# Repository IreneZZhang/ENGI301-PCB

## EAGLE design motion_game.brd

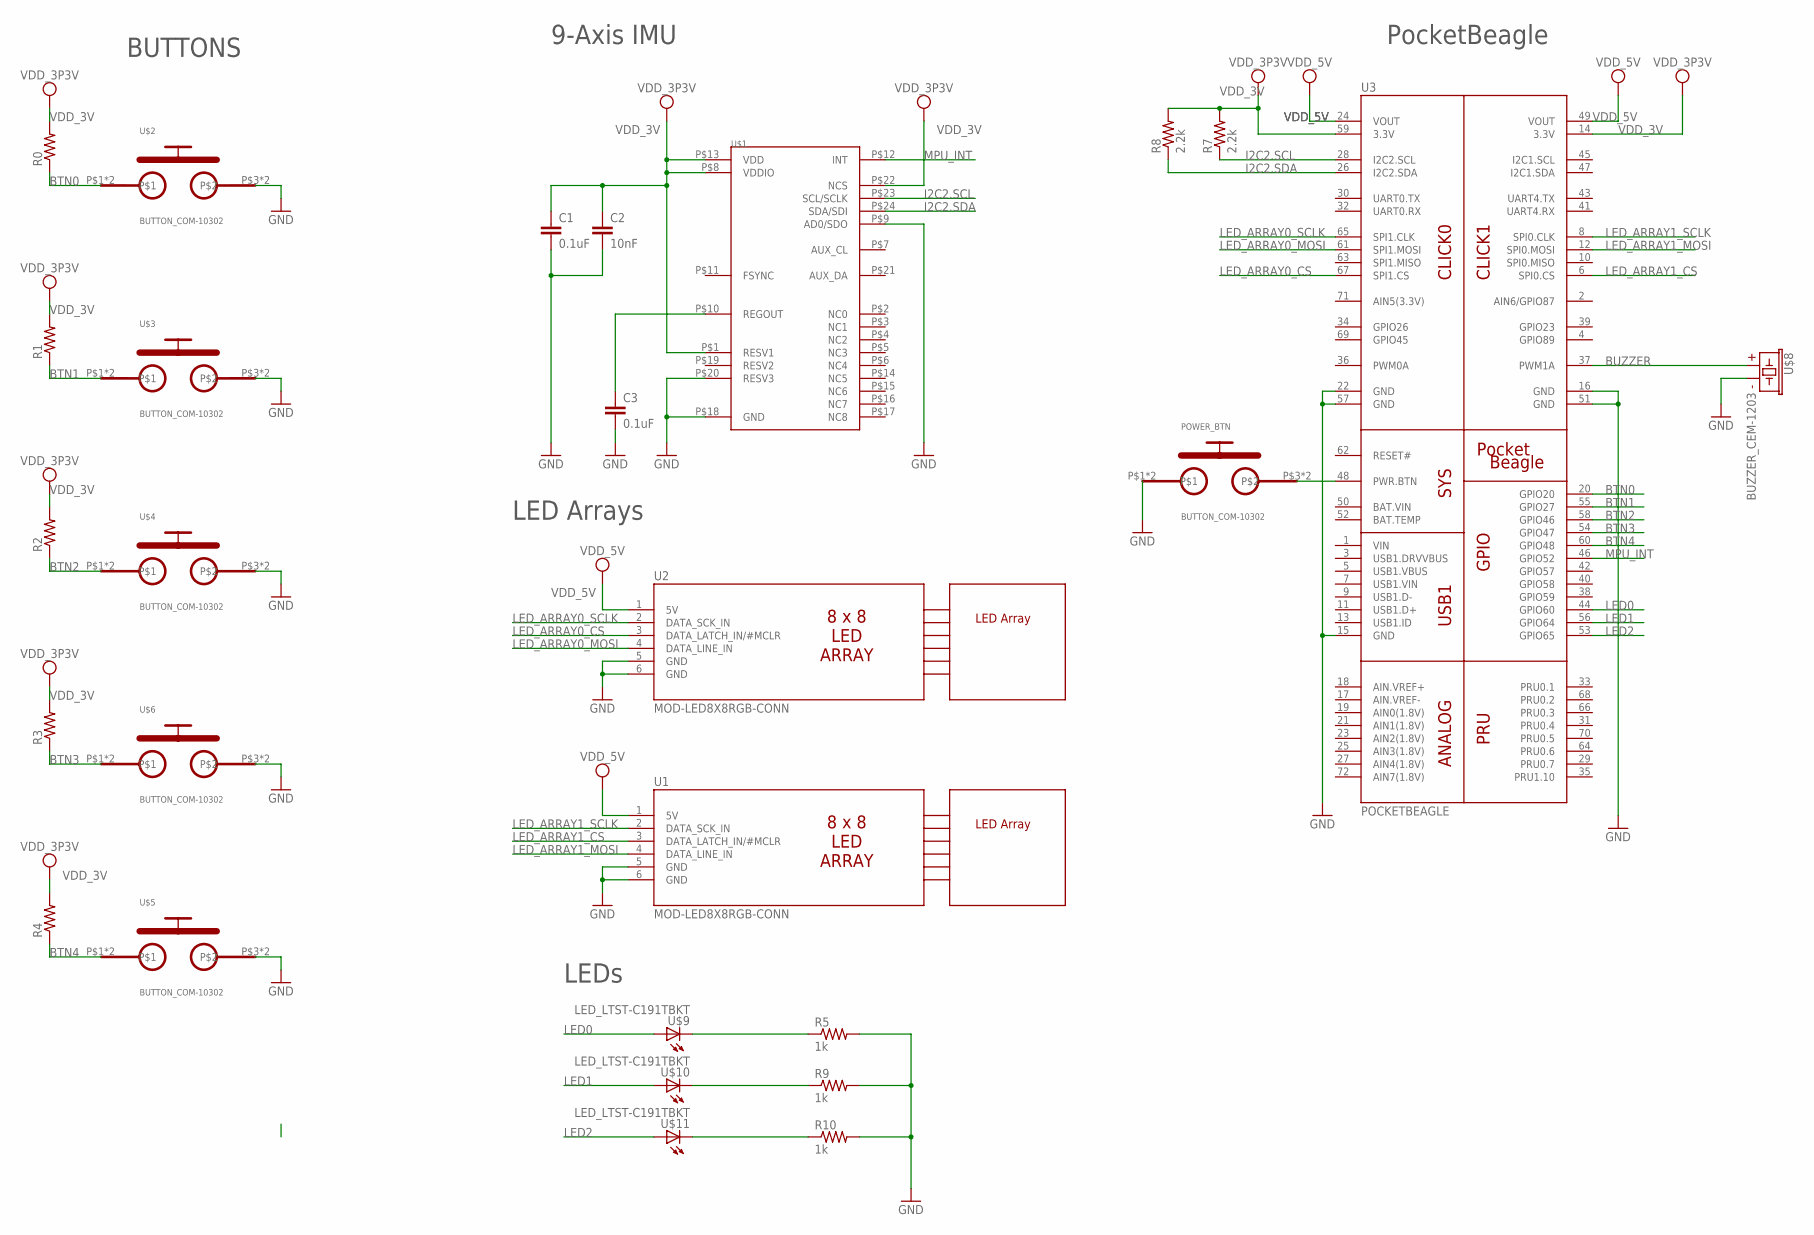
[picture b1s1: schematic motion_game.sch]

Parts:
C1, C3: 0.1uF; C0402
C2: 10nF; C0402
POWER_BTN: BUTTON_COM-10302; BUTTON_12.5MM
R0, R1, R2, R3, R4: R_R0603; R0603
R5, R9, R10: 1k; R0603
R7, R8: 2.2k; R0603
U1, U2: MOD-LED8X8RGB-CONN; FE06W
U3: POCKETBEAGLE
U$1: MPU-9250; QFN3X3MM
U$2, U$3, U$4, U$5, U$6: BUTTON_COM-10302; BUTTON_12.5MM
U$7, U$12: MOD-LED8X8RGB-OUTLINE; MOD-LED8X8RGB
U$8: BUZZER_CEM-1203; BUZZER_6.5MM
U$9, U$10, U$11: LED_LTST-C191TBKT; LED_EIA-STD

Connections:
BTN0: R0.1, U3.20 (GPIO20), U$2.P$1, U$2.P$2
BTN1: R1.1, U3.55 (GPIO27), U$3.P$1, U$3.P$2
BTN2: R2.1, U3.58 (GPIO46), U$4.P$1, U$4.P$2
BTN3: R3.1, U3.54 (GPIO47), U$6.P$1, U$6.P$2
BTN4: R4.1, U3.60 (GPIO48), U$5.P$1, U$5.P$2
BUZZER: U3.37 (PWM1A), U$8.P$2 (1)
GND: C1.2, C2.2, C3.2, POWER_BTN.P$1, POWER_BTN.P$2, R5.2, R9.2, R10.2, U1.5 (GND), U1.6 (GND), U2.5 (GND), U2.6 (GND), U3.15 (GND), U3.16 (GND), U3.22 (GND), U3.51 (GND), U3.57 (GND), U$1.P$9 (AD0/SDO), U$1.P$18 (GND), U$1.P$20 (RESV3), U$2.P$3, U$2.P$4, U$3.P$3, U$3.P$4, U$4.P$3, U$4.P$4, U$5.P$3, U$5.P$4, U$6.P$3, U$6.P$4, U$8.P$1 (2)
I2C2.SCL: R7.1, U3.28 (I2C2.SCL), U$1.P$23 (SCL/SCLK)
I2C2.SDA: R8.1, U3.26 (I2C2.SDA), U$1.P$24 (SDA/SDI)
LED0: U3.44 (GPIO60), U$9.P$1 (A)
LED1: U3.56 (GPIO64), U$10.P$1 (A)
LED2: U3.53 (GPIO65), U$11.P$1 (A)
LED_ARRAY0_CS: U2.3 (DATA_LATCH_IN/#MCLR), U3.67 (SPI1.CS)
LED_ARRAY0_MOSI: U2.4 (DATA_LINE_IN), U3.61 (SPI1.MOSI)
LED_ARRAY0_SCLK: U2.2 (DATA_SCK_IN), U3.65 (SPI1.CLK)
LED_ARRAY1_CS: U1.3 (DATA_LATCH_IN/#MCLR), U3.6 (SPI0.CS)
LED_ARRAY1_MOSI: U1.4 (DATA_LINE_IN), U3.12 (SPI0.MOSI)
LED_ARRAY1_SCLK: U1.2 (DATA_SCK_IN), U3.8 (SPI0.CLK)
MPU_INT: U3.46 (GPIO52), U$1.P$12 (INT)
unnamed: R5.1, U$9.P$2 (C)
unnamed: POWER_BTN.P$3, POWER_BTN.P$4, U3.48 (PWR.BTN)
unnamed: C3.1, U$1.P$10 (REGOUT)
unnamed: R9.1, U$10.P$2 (C)
unnamed: R10.1, U$11.P$2 (C)
VDD_3V: C1.1, C2.1, R0.2, R1.2, R2.2, R3.2, R4.2, R7.2, R8.2, U3.14 (3.3V), U3.59 (3.3V), U$1.P$1 (RESV1), U$1.P$8 (VDDIO), U$1.P$13 (VDD), U$1.P$22 (NCS)
VDD_5V: U1.1 (5V), U2.1 (5V), U3.24 (VOUT), U3.49 (VOUT)

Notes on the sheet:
BUTTONS
9-Axis IMU
LED Arrays
LEDs
PocketBeagle

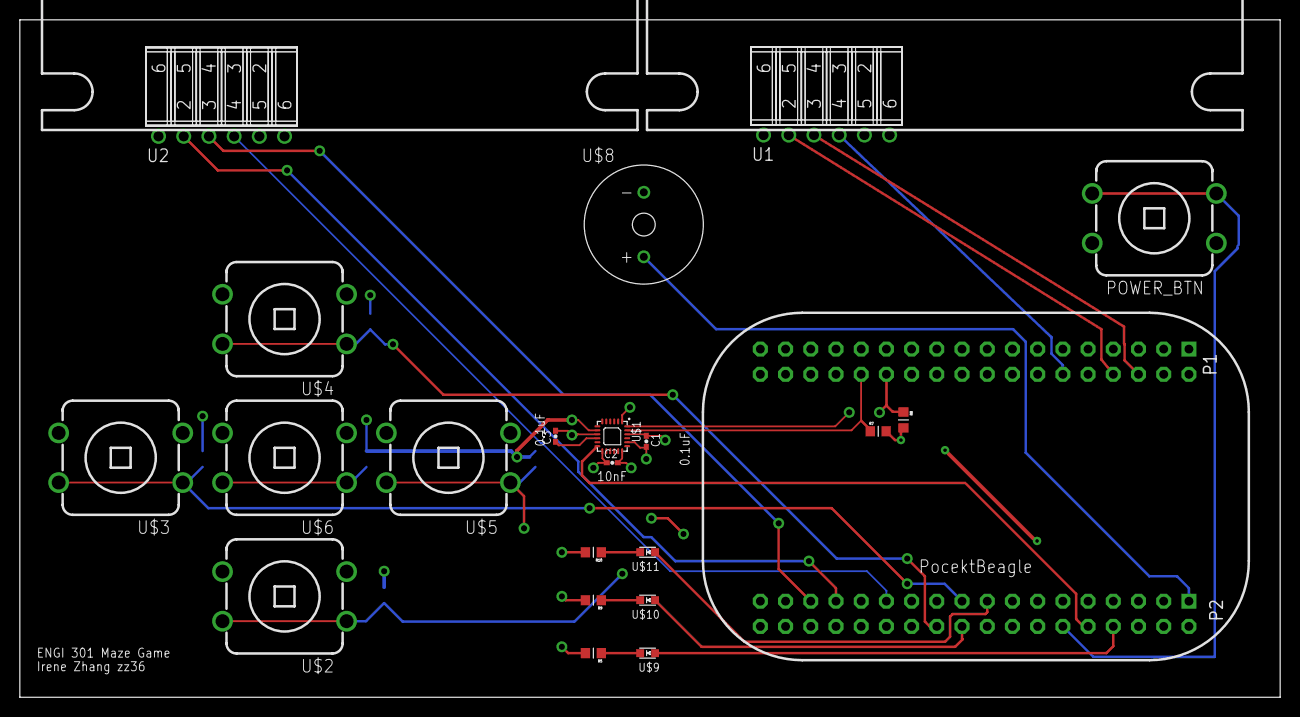
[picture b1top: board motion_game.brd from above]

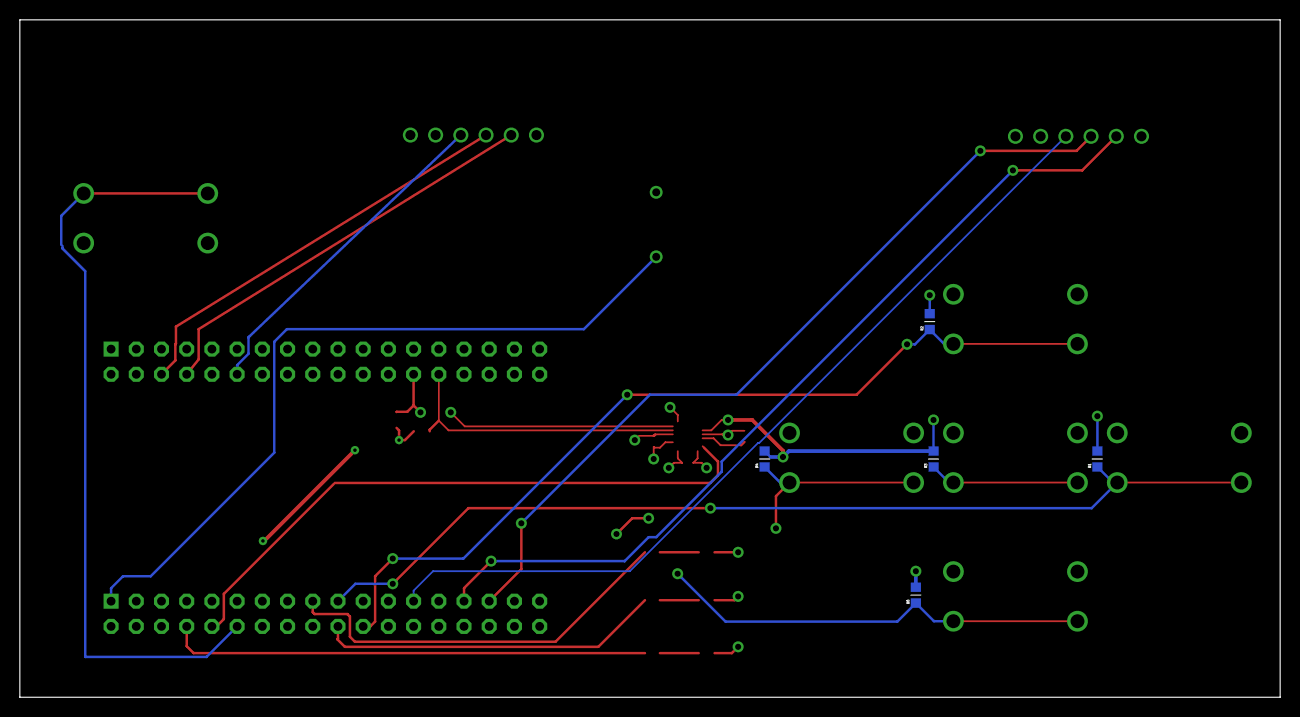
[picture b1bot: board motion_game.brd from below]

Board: 4 copper layers, 127.0 x 68.2 mm, 29 parts (5 on the bottom side), 26 nets.

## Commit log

2018-04-06 add 3 devices
2018-04-06 add parts
2018-04-06 add name and value
2018-04-22 route pdb
2018-04-25 add gerber files
2018-05-07 adjust Vdd
